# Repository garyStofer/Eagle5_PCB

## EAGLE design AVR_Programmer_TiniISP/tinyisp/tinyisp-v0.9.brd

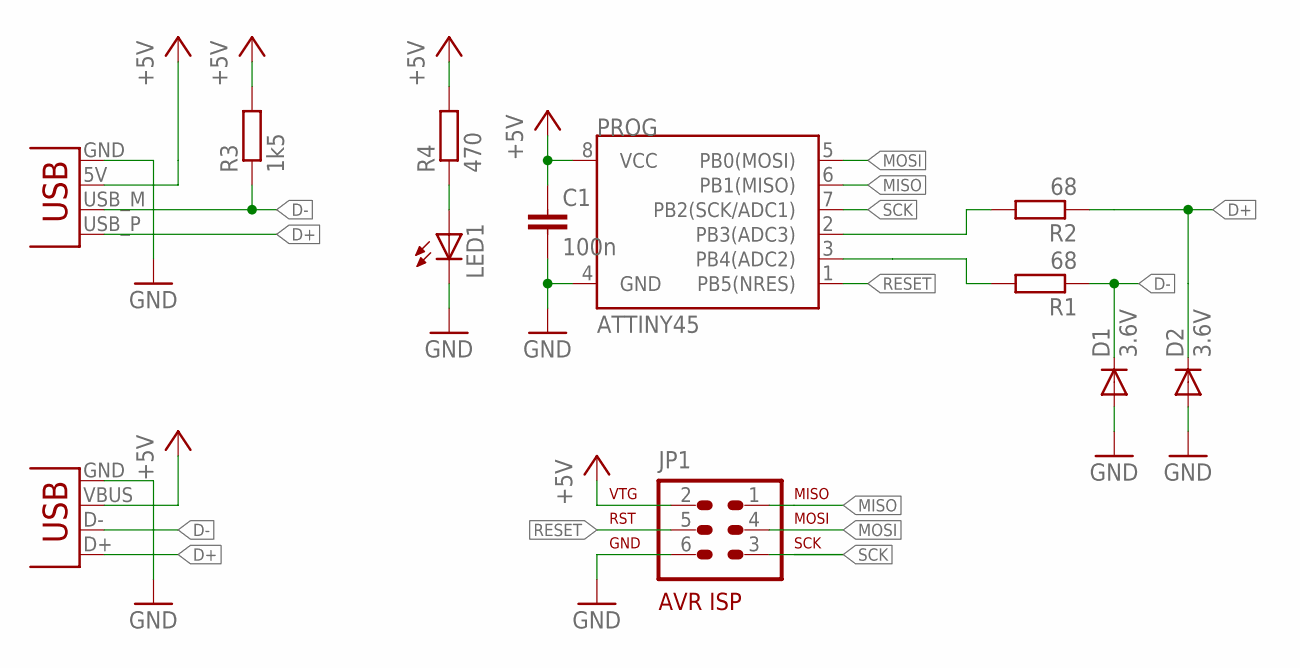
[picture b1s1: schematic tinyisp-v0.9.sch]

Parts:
C1: 100n; C0805
D1, D2: 3.6V; MINIMELF
JP1: AVR-ISP-6
LED1: LEDCHIP-LED0805; CHIP-LED0805
PROG: ATTINY45; SO08-EIAJ
R1, R2: 68; R0805
R3: 1k5; R0805
R4: 470; R0805
X1: USBPCB; USB-A-PCB
X2: USBMINI_B_NOHOLES; USB_MINI_B_NOHOLES

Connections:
+5V: C1.1, JP1.2, PROG.8 (VCC), R3.2, R4.2, X1.5V (VBUS), X2.VBUS
D+: D2.C, R2.1, X1.USB_P (D+), X2.D+
D-: D1.C, R1.1, R3.1, X1.USB_M (D-), X2.D-
GND: C1.2, D1.A, D2.A, JP1.6, LED1.C, PROG.4 (GND), X1.GND, X2.GND
MISO: JP1.1, PROG.6 (PB1(MISO))
MOSI: JP1.4, PROG.5 (PB0(MOSI))
unnamed: LED1.A, R4.1
unnamed: PROG.2 (PB3(ADC3)), R2.2
unnamed: PROG.3 (PB4(ADC2)), R1.2
RESET: JP1.5, PROG.1 (PB5(NRES))
SCK: JP1.3, PROG.7 (PB2(SCK/ADC1))

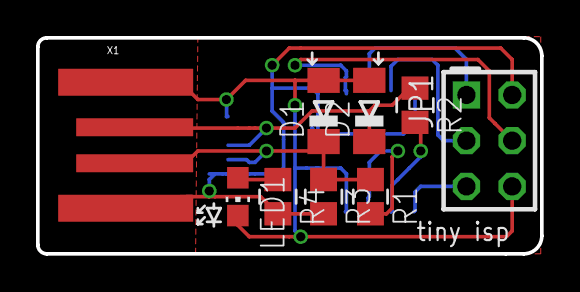
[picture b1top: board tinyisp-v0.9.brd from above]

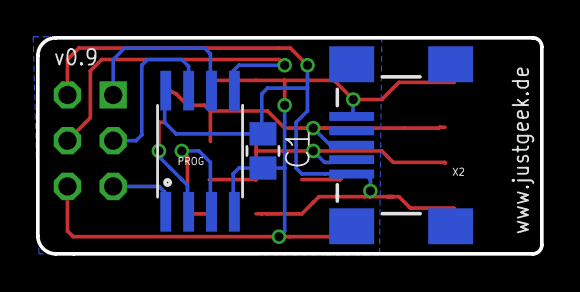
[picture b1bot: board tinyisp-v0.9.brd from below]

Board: 2 copper layers, 28.0 x 12.0 mm, 12 parts (3 on the bottom side), 11 nets.

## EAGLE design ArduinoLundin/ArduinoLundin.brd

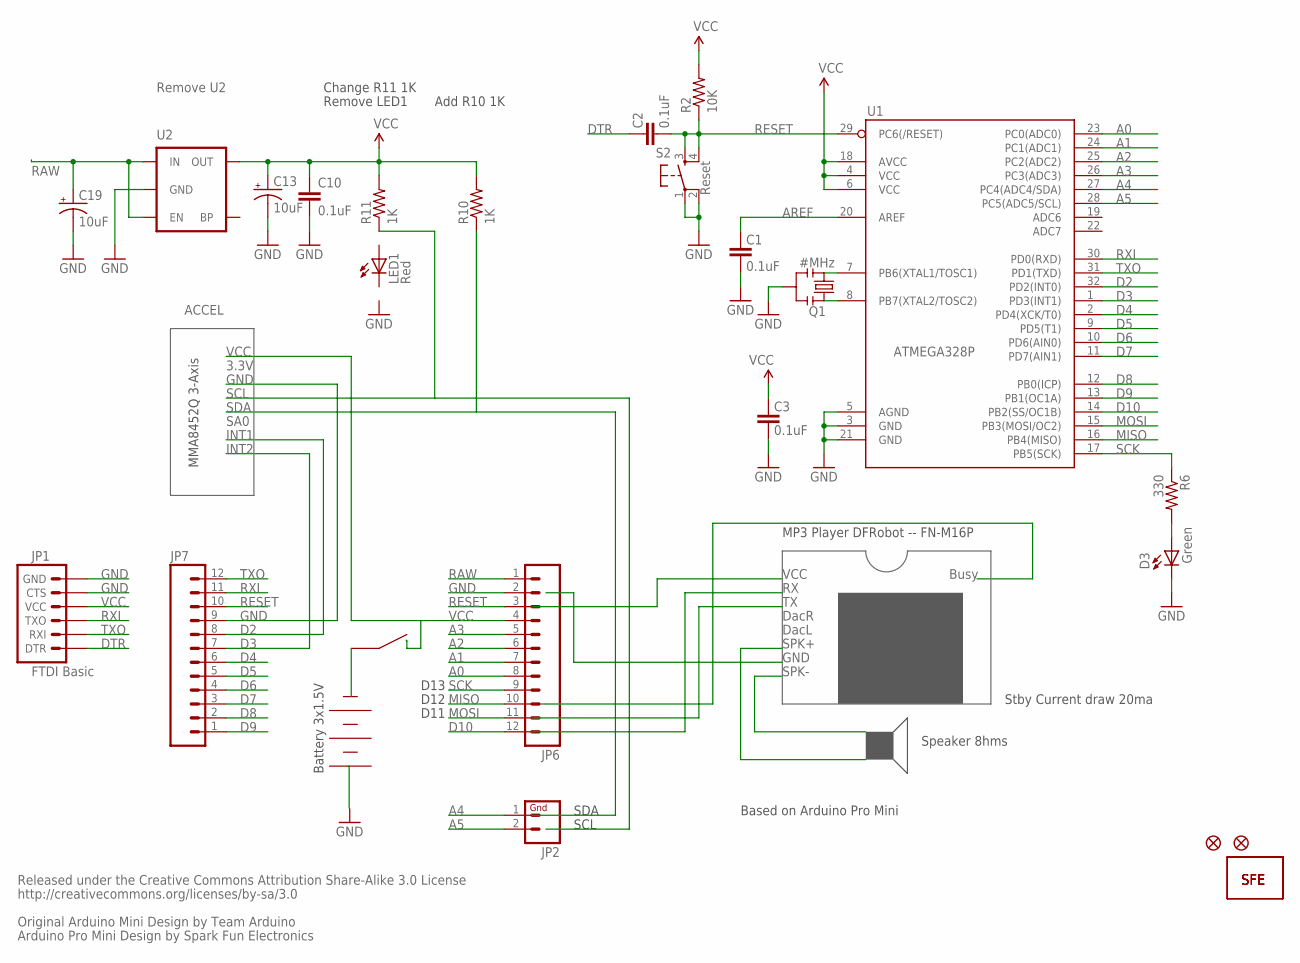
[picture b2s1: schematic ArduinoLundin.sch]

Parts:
C1, C2, C3, C10: 0.1uF; C0402
C13, C19: 10uF; EIA3216
D3: Green; LED-0603
JP1: FTDI Basic; 1X06
JP2: M02PTH; 1X02
JP6, JP7: M12PTH; 1X12
LED1: Red; LED-0603
Q1: #MHz; RESONATOR-SMD
R2: 10K; C0402
R6: 330; C0402
R10, R11: 1K; C0402
S2: Reset; TACTILE_SWITCH_SMD
U1: ATMEGA168#; TQFP32-08
U2: ###V; SOT23-5
U$1: LOGO-SFESK; SFE-LOGO-FLAME
U$2, U$4: FIDUCIAL1X2; FIDUCIAL-1X2
U$11: LOGO-SFENEW; SFE-NEW-WEBLOGO

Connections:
A0: JP6.8, U1.23 (PC0(ADC0))
A1: JP6.7, U1.24 (PC1(ADC1))
A2: JP6.6, U1.25 (PC2(ADC2))
A3: JP6.5, U1.26 (PC3(ADC3))
A4: JP2.1, U1.27 (PC4(ADC4/SDA))
A5: JP2.2, U1.28 (PC5(ADC5/SCL))
AREF: C1.2, U1.20 (AREF)
D2: JP7.8, U1.32 (PD2(INT0))
D3: JP7.7, U1.1 (PD3(INT1))
D4: JP7.6, U1.2 (PD4(XCK/T0))
D5: JP7.5, U1.9 (PD5(T1))
D6: JP7.4, U1.10 (PD6(AIN0))
D7: JP7.3, U1.11 (PD7(AIN1))
D8: JP7.2, U1.12 (PB0(ICP))
D9: JP7.1, U1.13 (PB1(OC1A))
D10: JP6.12, U1.14 (PB2(SS/OC1B))
DTR: C2.2, JP1.1 (DTR)
GND: C1.1, C3.1, C10.2, C13.C (-), C19.C (-), D3.C, JP1.5 (CTS), JP1.6 (GND), JP6.2, JP7.9, Q1.2, S2.1, S2.2, U1.3 (GND), U1.5 (AGND), U1.21 (GND), U2.2 (GND)
MISO: JP6.10, U1.16 (PB4(MISO))
MOSI: JP6.11, U1.15 (PB3(MOSI/OC2))
unnamed: Q1.1, U1.8 (PB7(XTAL2/TOSC2))
unnamed: Q1.3, U1.7 (PB6(XTAL1/TOSC1))
unnamed: D3.A, R6.2
unnamed: C19.A (+), U2.1 (IN), U2.3 (EN)
RAW: JP6.1
RESET: C2.1, JP6.3, JP7.10, R2.1, S2.3, S2.4, U1.29 (PC6(/RESET))
RXI: JP1.3 (TXO), JP7.11, U1.30 (PD0(RXD))
SCK: JP6.9, R6.1, U1.17 (PB5(SCK))
TXO: JP1.2 (RXI), JP7.12, U1.31 (PD1(TXD))
VCC: C3.2, C10.1, C13.A (+), JP1.4 (VCC), JP6.4, R2.2, R10.2, R11.2, U1.4 (VCC), U1.6 (VCC), U1.18 (AVCC), U2.5 (OUT)

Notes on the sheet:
Released under the Creative Commons Attribution Share-Alike 3.0 License
http://creativecommons.org/licenses/by-sa/3.0
Original Arduino Mini Design by Team Arduino
Arduino Pro Mini Design by Spark Fun Electronics
ACCEL
VCC
3.3V
GND
SCL
SDA
SA0
INT1
INT2
DacR
DacL
SPK+
SPK-
Busy
Remove U2
Remove LED1
RAW
Change R11 1K
Add R10 1K
D11
D13
D12
Speaker 8hms
MP3 Player DFRobot -- FN-M16P
MMA8452Q 3-Axis
Battery 3x1.5V
Based on Arduino Pro Mini
Stby Current draw 20ma
ATMEGA328P

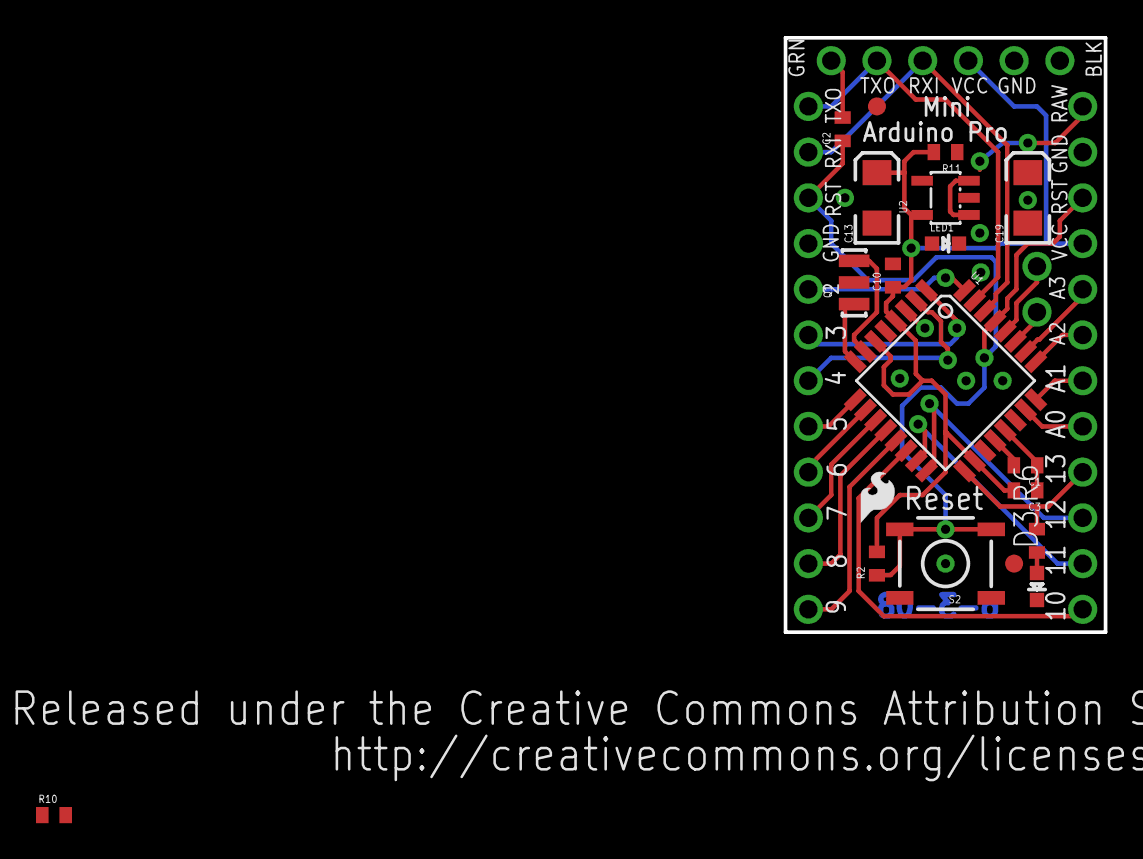
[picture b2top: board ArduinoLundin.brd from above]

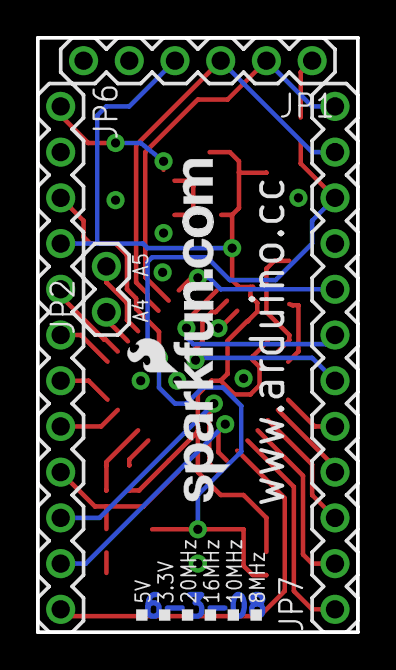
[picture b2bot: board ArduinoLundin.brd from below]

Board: 2 copper layers, 17.8 x 33.0 mm, 24 parts (5 on the bottom side), 29 nets.

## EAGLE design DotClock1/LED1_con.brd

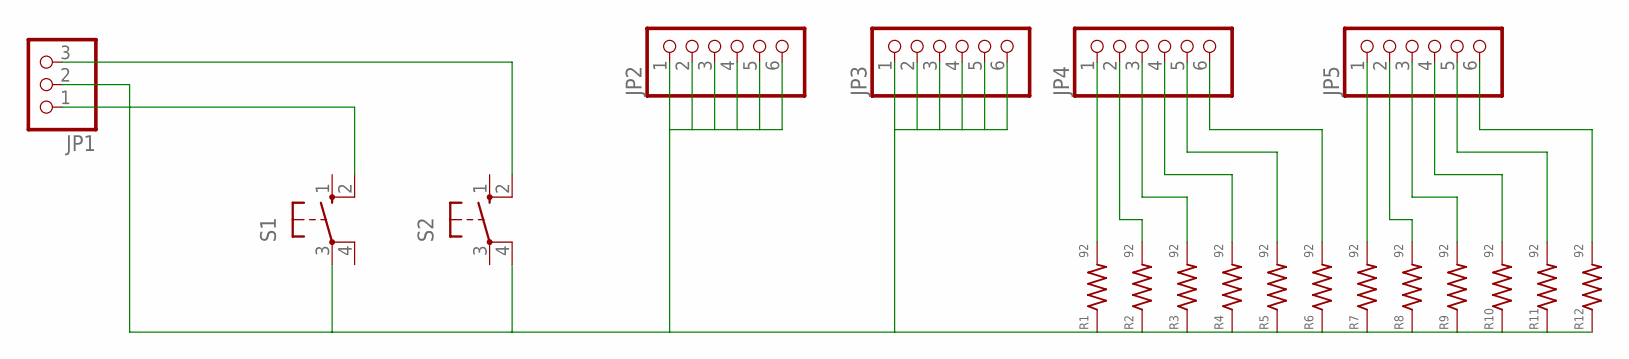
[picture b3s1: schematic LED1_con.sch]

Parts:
JP1: PINHD-1X3; 1X03
JP2, JP3, JP4, JP5: PINHD-1X6; 1X06
R1, R2, R3, R4, R5, R6, R7, R8, R9, R10, R11, R12: 92; R1206
S1, S2: 10-XX; B3F-10XX

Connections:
unnamed: JP1.3, S2.2 (S1)
unnamed: JP1.1, S1.2 (S1)
unnamed: JP1.2, JP2.1, JP2.2, JP2.3, JP2.4, JP2.5, JP2.6, JP3.1, JP3.2, JP3.3, JP3.4, JP3.5, JP3.6, R1.1, R2.1, R3.1, R4.1, R5.1, R6.1, R7.1, R8.1, R9.1, R10.1, R11.1, R12.1, S1.3, S2.4 (P1)
unnamed: JP4.1, R1.2
unnamed: JP4.2, R2.2
unnamed: JP4.3, R3.2
unnamed: JP4.4, R4.2
unnamed: JP4.5, R5.2
unnamed: JP4.6, R6.2
unnamed: JP5.1, R7.2
unnamed: JP5.2, R8.2
unnamed: JP5.3, R9.2
unnamed: JP5.4, R10.2
unnamed: JP5.5, R11.2
unnamed: JP5.6, R12.2

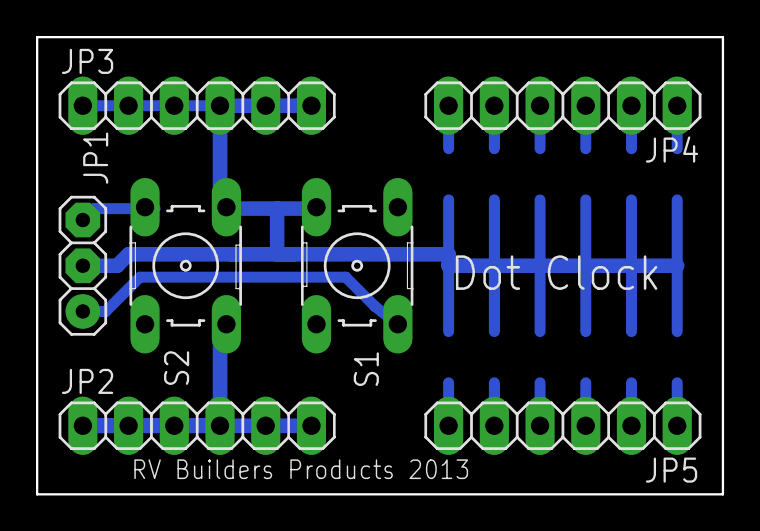
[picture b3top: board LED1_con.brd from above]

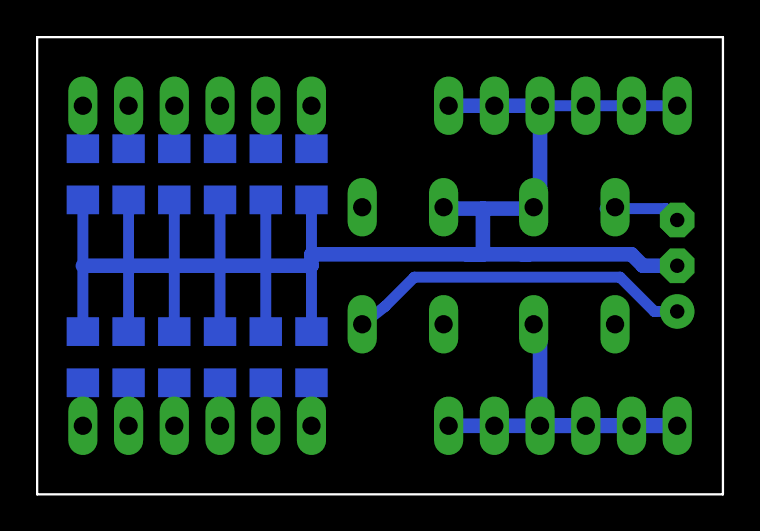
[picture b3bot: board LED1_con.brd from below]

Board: 2 copper layers, 38.1 x 25.4 mm, 19 parts (12 on the bottom side), 15 nets.
